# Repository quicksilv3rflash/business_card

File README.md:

# business_card
A nifty business card!

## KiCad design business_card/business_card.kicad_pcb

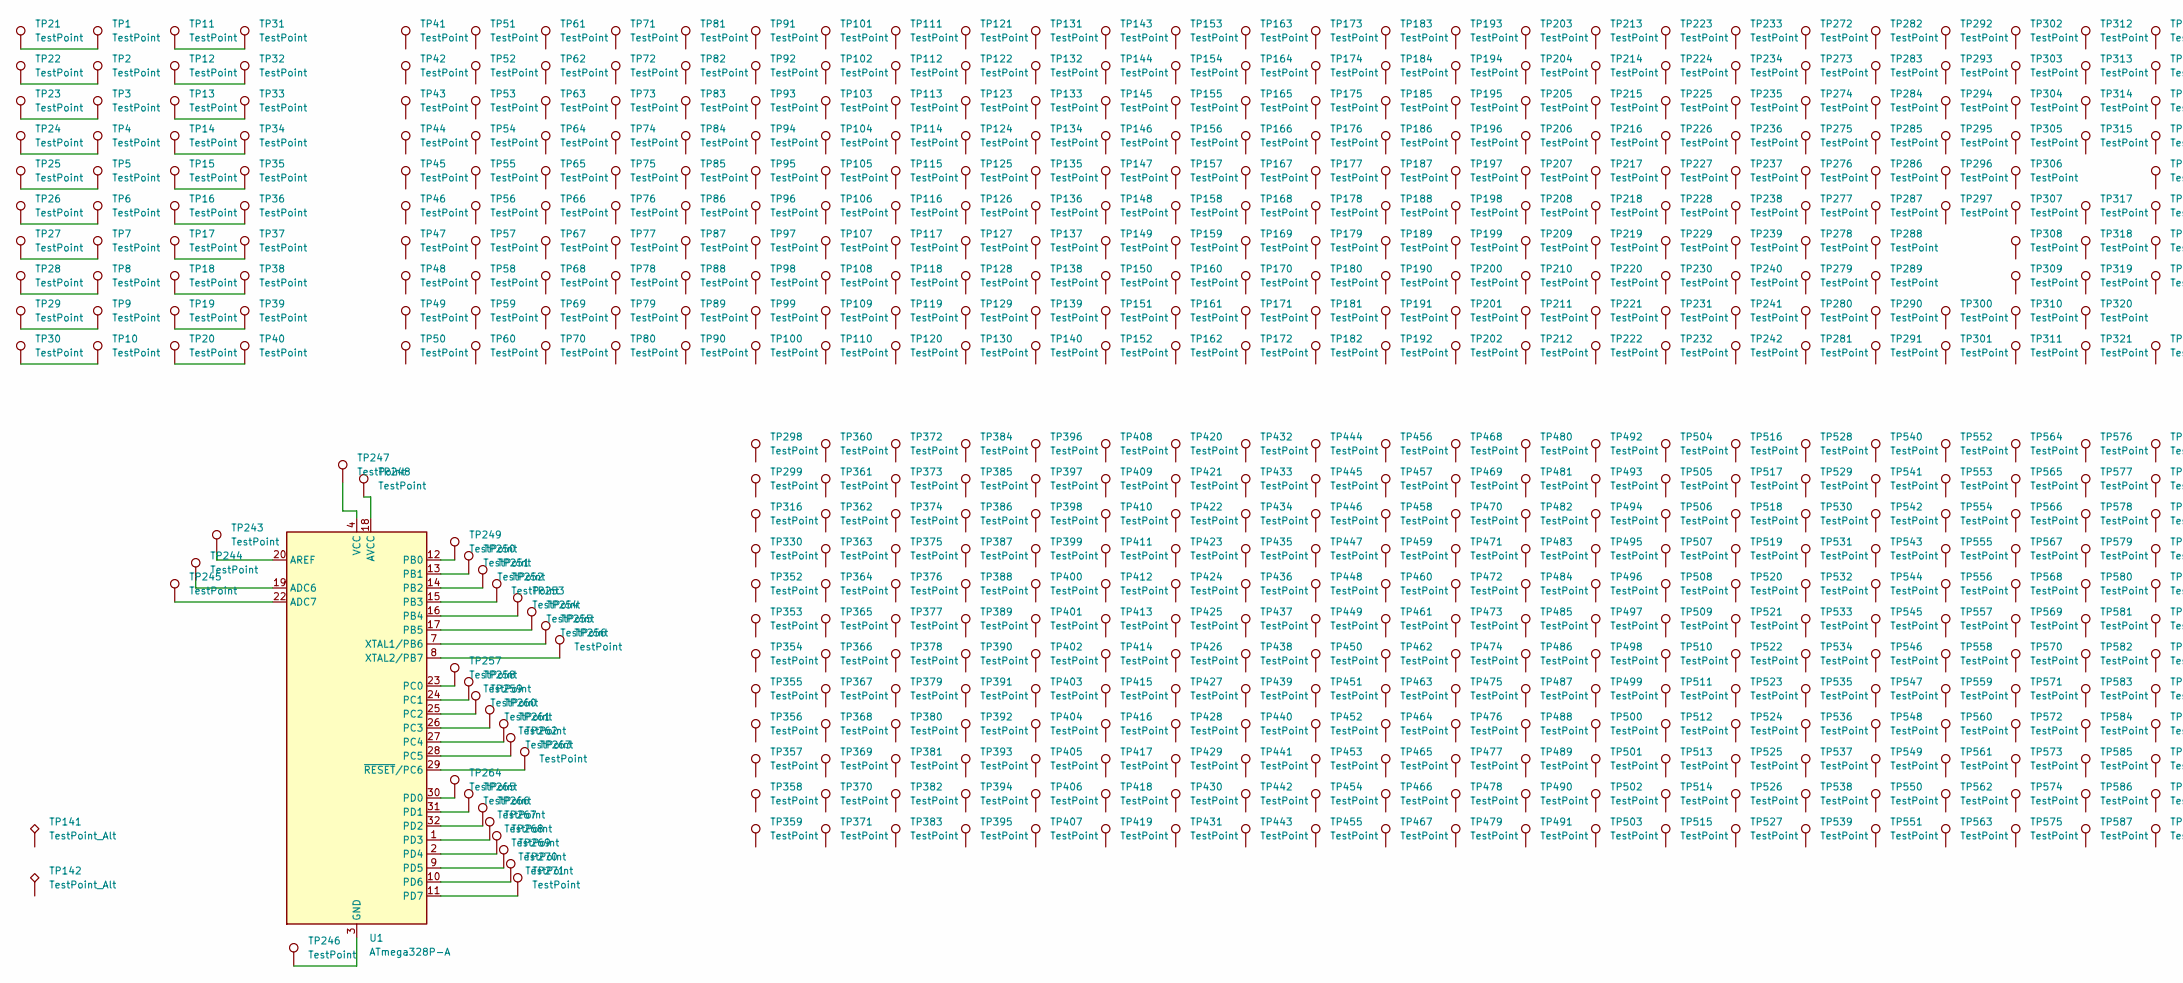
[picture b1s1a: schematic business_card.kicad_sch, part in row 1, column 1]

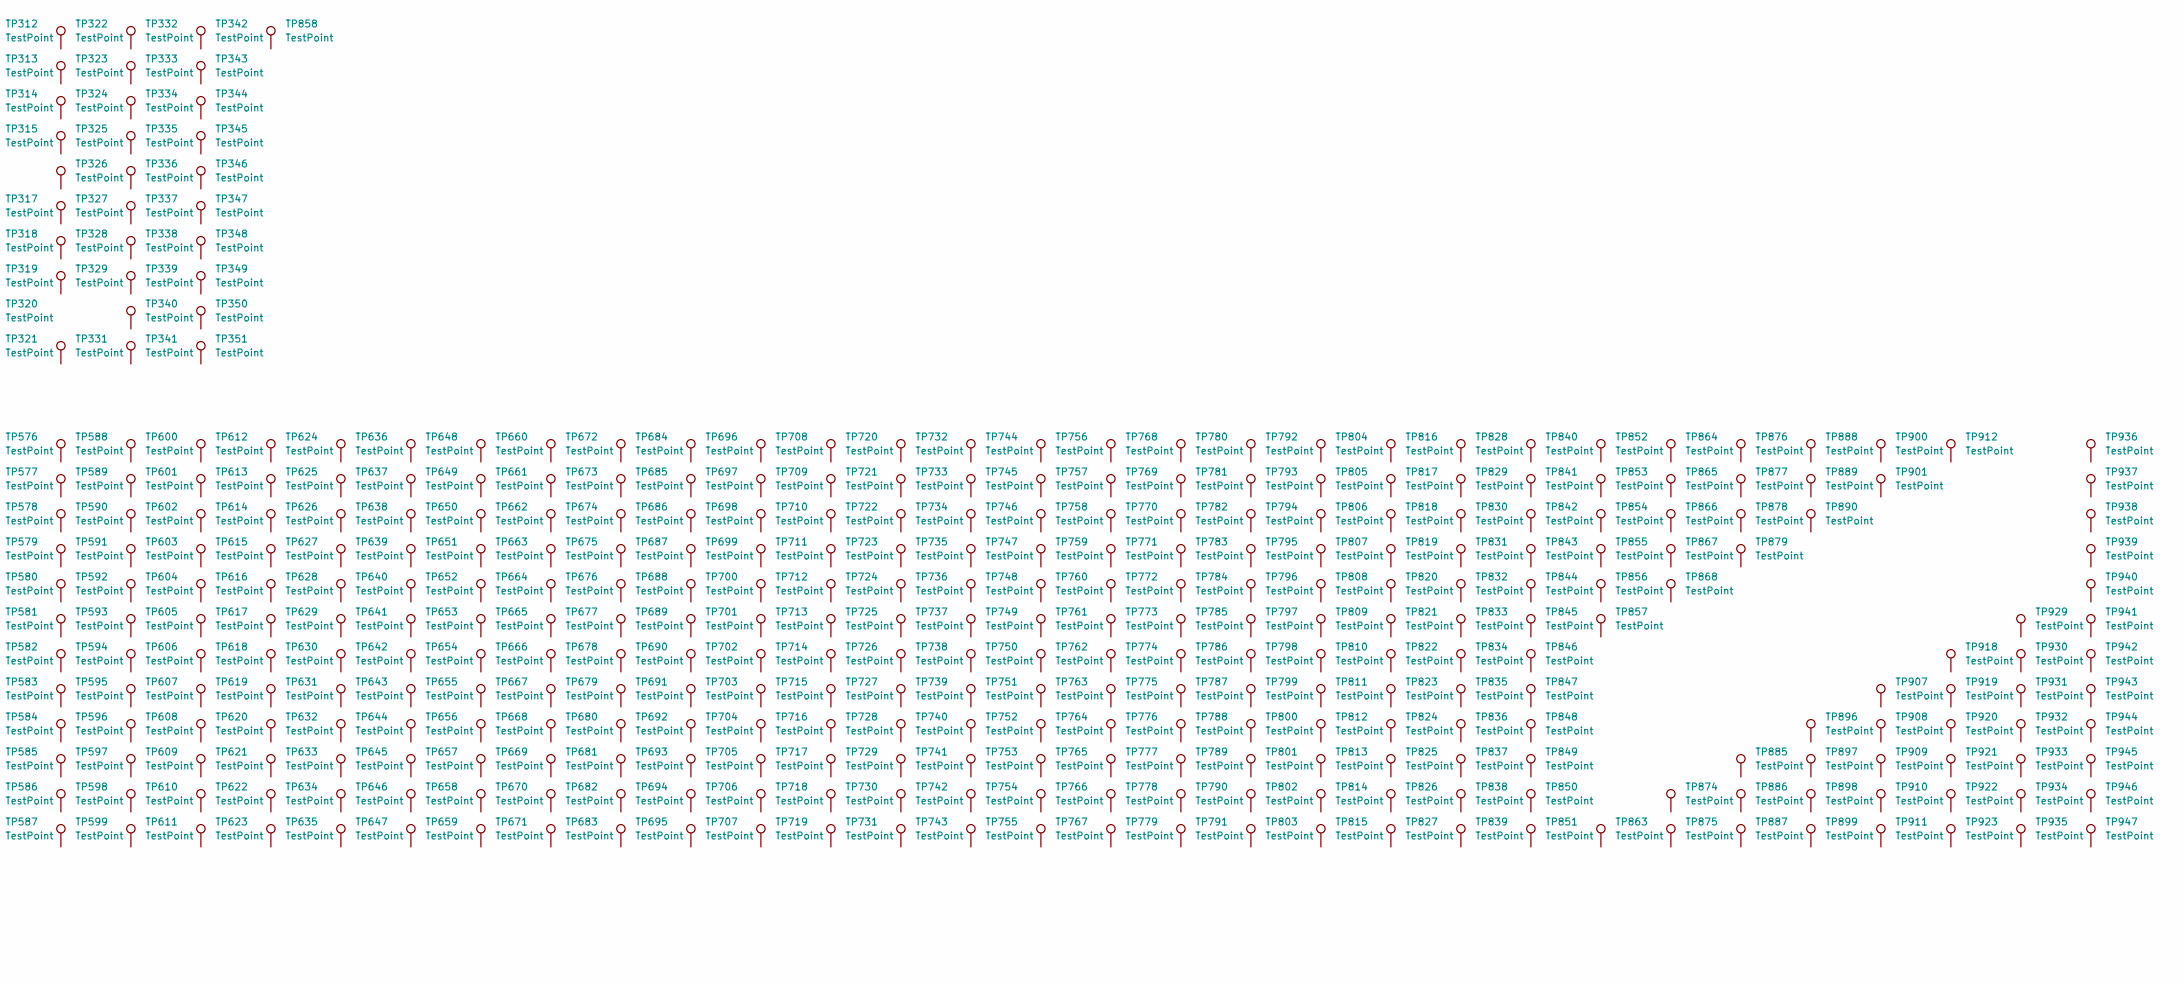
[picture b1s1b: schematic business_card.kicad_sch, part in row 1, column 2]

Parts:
TP1, TP2, TP3, TP4, TP5, TP6, TP7, TP8, TP9, TP10, TP11, TP12, TP13, TP14, TP15, TP16, TP17, TP18, TP19, TP20: TestPoint; TestPoint_Plated_Hole_D2.0mm
TP21, TP22, TP23, TP24, TP25, TP26, TP27, TP28, TP29, TP30, TP31, TP32, TP33, TP34, TP35, TP36, TP37, TP38, TP39, TP40, TP41, TP42, TP43, TP44, TP45, TP46, TP47, TP48, TP49, TP50, TP51, TP52, TP53, TP54, TP55, TP56, TP57, TP58, TP59, TP60, TP61, TP62, TP63, TP64, TP65, TP66, TP67, TP68, TP69, TP70, TP71, TP72, TP73, TP74, TP75, TP76, TP77, TP78, TP79, TP80, TP81, TP82, TP83, TP84, TP85, TP86, TP87, TP88, TP89, TP90, TP91, TP92, TP93, TP94, TP95, TP96, TP97, TP98, TP99, TP100, TP101, TP102, TP103, TP104, TP105, TP106, TP107, TP108, TP109, TP110, TP111, TP112, TP113, TP114, TP115, TP116, TP117, TP118, TP119, TP120, TP121, TP122, TP123, TP124, TP125, TP126, TP127, TP128, TP129, TP130, TP131, TP132, TP133, TP134, TP135, TP136, TP137, TP138, TP139, TP140, TP143, TP144, TP145, TP146, TP147, TP148, TP149, TP150, TP151, TP152, TP153, TP154, TP155, TP156, TP157, TP158, TP159, TP160, TP161, TP162, TP163, TP164, TP165, TP166, TP167, TP168, TP169, TP170, TP171, TP172, TP173, TP174, TP175, TP176, TP177, TP178, TP179, TP180, TP181, TP182, TP183, TP184, TP185, TP186, TP187, TP188, TP189, TP190, TP191, TP192, TP193, TP194, TP195, TP196, TP197, TP198, TP199, TP200, TP201, TP202, TP203, TP204, TP205, TP206, TP207, TP208, TP209, TP210, TP211, TP212, TP213, TP214, TP215, TP216, TP217, TP218, TP219, TP220, TP221, TP222, TP223, TP224, TP225, TP226, TP227, TP228, TP229, TP230, TP231, TP232, TP233, TP234, TP235, TP236, TP237, TP238, TP239, TP240, TP241, TP242, TP243, TP244, TP245, TP246, TP247, TP248, TP249, TP250, TP251, TP252, TP253, TP254, TP255, TP256, TP257, TP258, TP259, TP260, TP261, TP262, TP263, TP264, TP265, TP266, TP267, TP268, TP269, TP270, TP271, TP272, TP273, TP274, TP275, TP276, TP277, TP278, TP279, TP280, TP281, TP282, TP283, TP284, TP285, TP286, TP287, TP288, TP289, TP290, TP291, TP292, TP293, TP294, TP295, TP296, TP297, TP300, TP301, TP302, TP303, TP304, TP305, TP306, TP307, TP308, TP309, TP310, TP311, TP312, TP313, TP314, TP315, TP317, TP318, TP319, TP320, TP321, TP322, TP323, TP324, TP325, TP326, TP327, TP328, TP329, TP331, TP332, TP333, TP334, TP335, TP336, TP337, TP338, TP339, TP340, TP341, TP342, TP343, TP344, TP345, TP346, TP347, TP348, TP349, TP350, TP351, TP858: TestPoint; TestPoint_THTPad_D2.0mm_Drill1.0mm
TP141: TestPoint_Alt; business_card_front
TP142: TestPoint_Alt; business_card_back
TP298, TP299, TP316, TP330, TP352, TP353, TP354, TP355, TP356, TP357, TP358, TP359, TP360, TP361, TP362, TP363, TP364, TP365, TP366, TP367, TP368, TP369, TP370, TP371, TP372, TP373, TP374, TP375, TP376, TP377, TP378, TP379, TP380, TP381, TP382, TP383, TP384, TP385, TP386, TP387, TP388, TP389, TP390, TP391, TP392, TP393, TP394, TP395, TP396, TP397, TP398, TP399, TP400, TP401, TP402, TP403, TP404, TP405, TP406, TP407, TP408, TP409, TP410, TP411, TP412, TP413, TP414, TP415, TP416, TP417, TP418, TP419, TP420, TP421, TP422, TP423, TP424, TP425, TP426, TP427, TP428, TP429, TP430, TP431, TP432, TP433, TP434, TP435, TP436, TP437, TP438, TP439, TP440, TP441, TP442, TP443, TP444, TP445, TP446, TP447, TP448, TP449, TP450, TP451, TP452, TP453, TP454, TP455, TP456, TP457, TP458, TP459, TP460, TP461, TP462, TP463, TP464, TP465, TP466, TP467, TP468, TP469, TP470, TP471, TP472, TP473, TP474, TP475, TP476, TP477, TP478, TP479, TP480, TP481, TP482, TP483, TP484, TP485, TP486, TP487, TP488, TP489, TP490, TP491, TP492, TP493, TP494, TP495, TP496, TP497, TP498, TP499, TP500, TP501, TP502, TP503, TP504, TP505, TP506, TP507, TP508, TP509, TP510, TP511, TP512, TP513, TP514, TP515, TP516, TP517, TP518, TP519, TP520, TP521, TP522, TP523, TP524, TP525, TP526, TP527, TP528, TP529, TP530, TP531, TP532, TP533, TP534, TP535, TP536, TP537, TP538, TP539, TP540, TP541, TP542, TP543, TP544, TP545, TP546, TP547, TP548, TP549, TP550, TP551, TP552, TP553, TP554, TP555, TP556, TP557, TP558, TP559, TP560, TP561, TP562, TP563, TP564, TP565, TP566, TP567, TP568, TP569, TP570, TP571, TP572, TP573, TP574, TP575, TP576, TP577, TP578, TP579, TP580, TP581, TP582, TP583, TP584, TP585, TP586, TP587, TP588, TP589, TP590, TP591, TP592, TP593, TP594, TP595, TP596, TP597, TP598, TP599, TP600, TP601, TP602, TP603, TP604, TP605, TP606, TP607, TP608, TP609, TP610, TP611, TP612, TP613, TP614, TP615, TP616, TP617, TP618, TP619, TP620, TP621, TP622, TP623, TP624, TP625, TP626, TP627, TP628, TP629, TP630, TP631, TP632, TP633, TP634, TP635, TP636, TP637, TP638, TP639, TP640, TP641, TP642, TP643, TP644, TP645, TP646, TP647, TP648, TP649, TP650, TP651, TP652, TP653, TP654, TP655, TP656, TP657, TP658, TP659, TP660, TP661, TP662, TP663, TP664, TP665, TP666, TP667, TP668, TP669, TP670, TP671, TP672, TP673, TP674, TP675, TP676, TP677, TP678, TP679, TP680, TP681, TP682, TP683, TP684, TP685, TP686, TP687, TP688, TP689, TP690, TP691, TP692, TP693, TP694, TP695, TP696, TP697, TP698, TP699, TP700, TP701, TP702, TP703, TP704, TP705, TP706, TP707, TP708, TP709, TP710, TP711, TP712, TP713, TP714, TP715, TP716, TP717, TP718, TP719, TP720, TP721, TP722, TP723, TP724, TP725, TP726, TP727, TP728, TP729, TP730, TP731, TP732, TP733, TP734, TP735, TP736, TP737, TP738, TP739, TP740, TP741, TP742, TP743, TP744, TP745, TP746, TP747, TP748, TP749, TP750, TP751, TP752, TP753, TP754, TP755, TP756, TP757, TP758, TP759, TP760, TP761, TP762, TP763, TP764, TP765, TP766, TP767, TP768, TP769, TP770, TP771, TP772, TP773, TP774, TP775, TP776, TP777, TP778, TP779, TP780, TP781, TP782, TP783, TP784, TP785, TP786, TP787, TP788, TP789, TP790, TP791, TP792, TP793, TP794, TP795, TP796, TP797, TP798, TP799, TP800, TP801, TP802, TP803, TP804, TP805, TP806, TP807, TP808, TP809, TP810, TP811, TP812, TP813, TP814, TP815, TP816, TP817, TP818, TP819, TP820, TP821, TP822, TP823, TP824, TP825, TP826, TP827, TP828, TP829, TP830, TP831, TP832, TP833, TP834, TP835, TP836, TP837, TP838, TP839, TP840, TP841, TP842, TP843, TP844, TP845, TP846, TP847, TP848, TP849, TP850, TP851, TP852, TP853, TP854, TP855, TP856, TP857, TP863, TP864, TP865, TP866, TP867, TP868, TP874, TP875, TP876, TP877, TP878, TP879, TP885, TP886, TP887, TP888, TP889, TP890, TP896, TP897, TP898, TP899, TP900, TP901, TP907, TP908, TP909, TP910, TP911, TP912, TP918, TP919, TP920, TP921, TP922, TP923, TP929, TP930, TP931, TP932, TP933, TP934, TP935, TP936, TP937, TP938, TP939, TP940, TP941, TP942, TP943, TP944, TP945, TP946, TP947: TestPoint; TestPoint_Pad_1.0x1.0mm
U1: ATmega328P-A; TQFP-32_7x7mm_P0.8mm

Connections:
unnamed: TP1.1, TP21.1
unnamed: TP2.1, TP22.1
unnamed: TP10.1, TP30.1
unnamed: TP11.1, TP31.1
unnamed: TP12.1, TP32.1
unnamed: TP13.1, TP33.1
unnamed: TP14.1, TP34.1
unnamed: TP15.1, TP35.1
unnamed: TP16.1, TP36.1
unnamed: TP17.1, TP37.1
unnamed: TP18.1, TP38.1
unnamed: TP19.1, TP39.1
unnamed: TP20.1, TP40.1
unnamed: TP3.1, TP23.1
unnamed: TP4.1, TP24.1
unnamed: TP5.1, TP25.1
unnamed: TP6.1, TP26.1
unnamed: TP7.1, TP27.1
unnamed: TP8.1, TP28.1
unnamed: TP9.1, TP29.1
unnamed: TP246.1, U1.3 (GND), U1.5 (GND), U1.21 (GND)
unnamed: TP247.1, U1.4 (VCC), U1.6 (VCC)
unnamed: TP244.1, U1.19 (ADC6)
unnamed: TP245.1, U1.22 (ADC7)
unnamed: TP243.1, U1.20 (AREF)
unnamed: TP248.1, U1.18 (AVCC)
unnamed: TP249.1, U1.12 (PB0)
unnamed: TP250.1, U1.13 (PB1)
unnamed: TP251.1, U1.14 (PB2)
unnamed: TP252.1, U1.15 (PB3)
unnamed: TP253.1, U1.16 (PB4)
unnamed: TP254.1, U1.17 (PB5)
unnamed: TP257.1, U1.23 (PC0)
unnamed: TP258.1, U1.24 (PC1)
unnamed: TP259.1, U1.25 (PC2)
unnamed: TP260.1, U1.26 (PC3)
unnamed: TP261.1, U1.27 (PC4)
unnamed: TP262.1, U1.28 (PC5)
unnamed: TP264.1, U1.30 (PD0)
unnamed: TP265.1, U1.31 (PD1)
unnamed: TP266.1, U1.32 (PD2)
unnamed: TP267.1, U1.1 (PD3)
unnamed: TP268.1, U1.2 (PD4)
unnamed: TP269.1, U1.9 (PD5)
unnamed: TP270.1, U1.10 (PD6)
unnamed: TP271.1, U1.11 (PD7)
unnamed: TP255.1, U1.7 (XTAL1/PB6)
unnamed: TP256.1, U1.8 (XTAL2/PB7)
unnamed: TP263.1, U1.29 (~RESET/PC6)

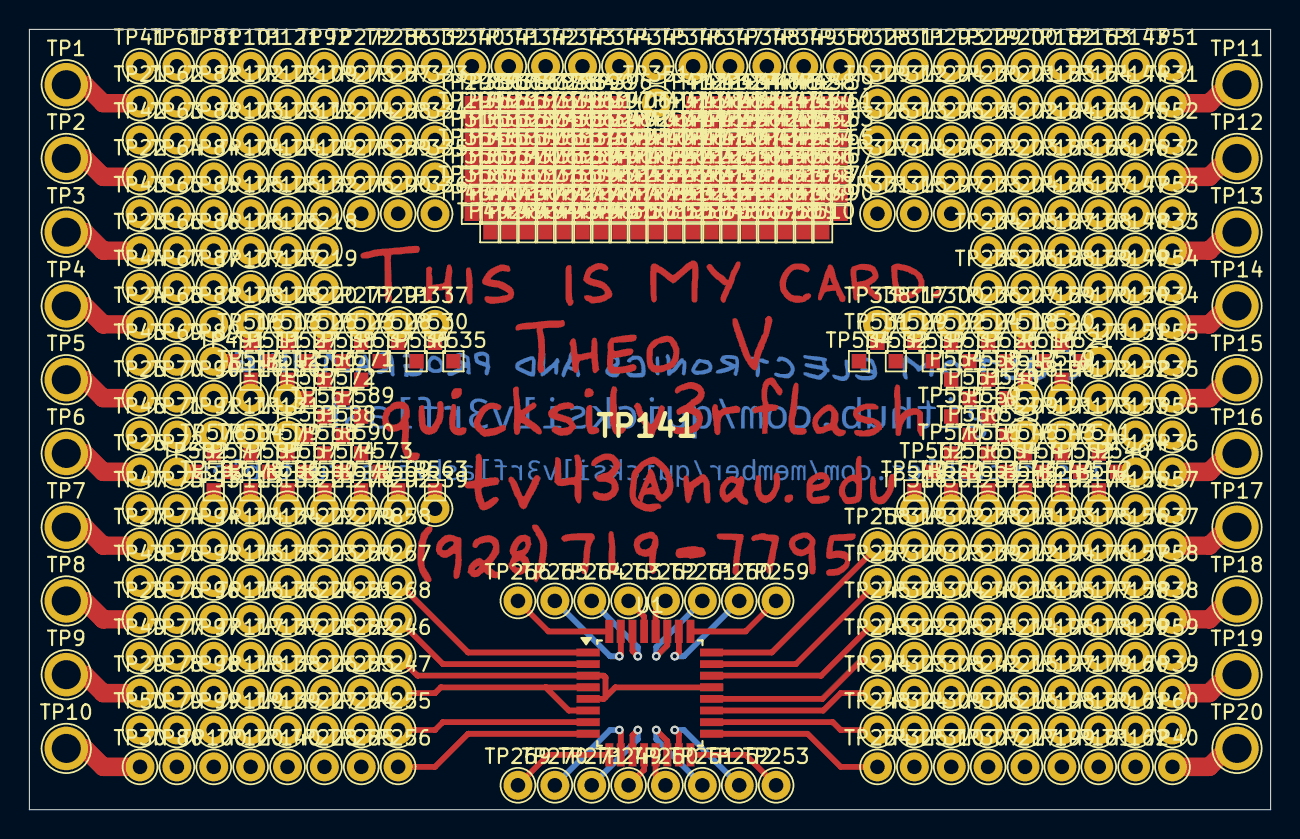
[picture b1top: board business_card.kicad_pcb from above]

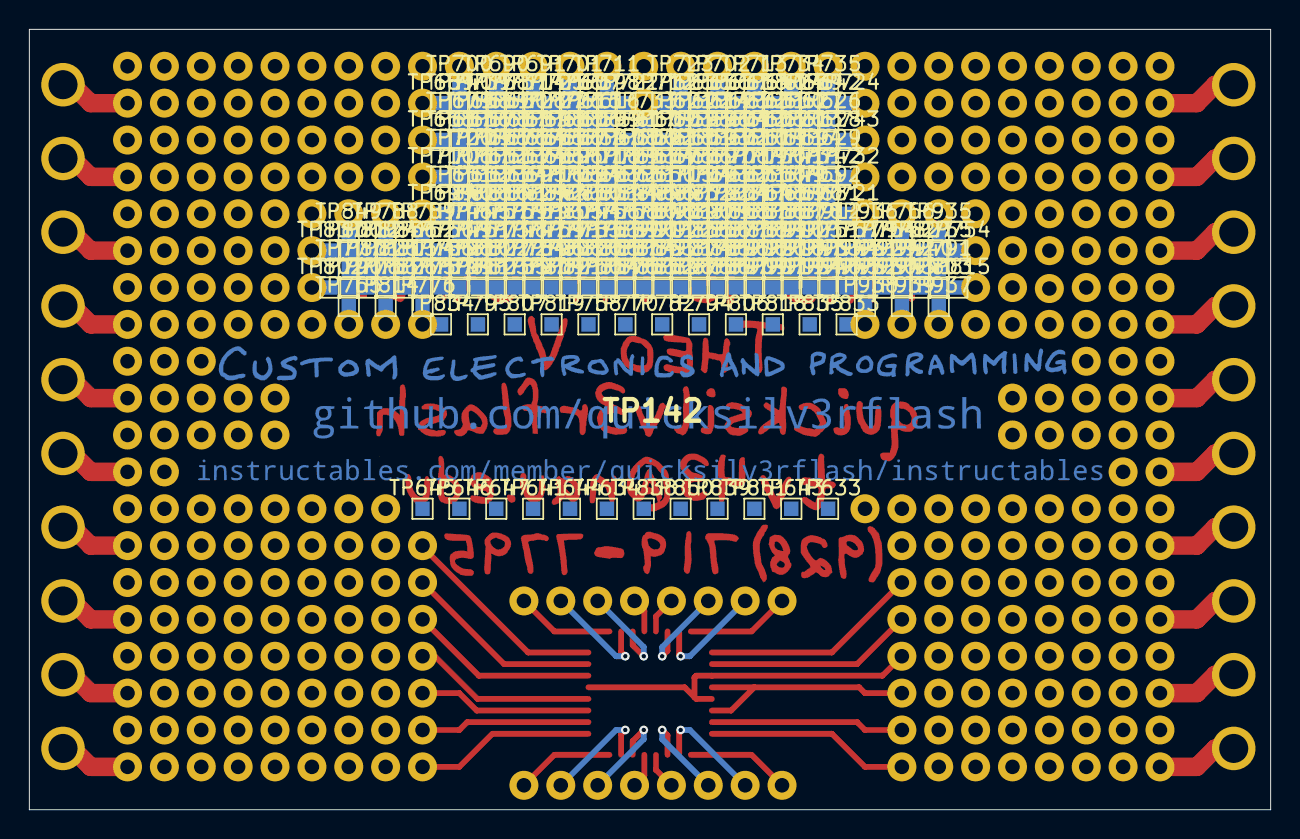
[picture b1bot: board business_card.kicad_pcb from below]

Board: 2 copper layers, 85.5 x 53.8 mm, 914 parts (323 on the bottom side), 49 nets.

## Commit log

2025-10-22 Upload preliminary project files
2025-10-22 Upload remaining project files
